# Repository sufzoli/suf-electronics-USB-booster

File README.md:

# suf-electronics-USB-booster
Boost power supply for inline conditioning of the 5V USB supply voltage

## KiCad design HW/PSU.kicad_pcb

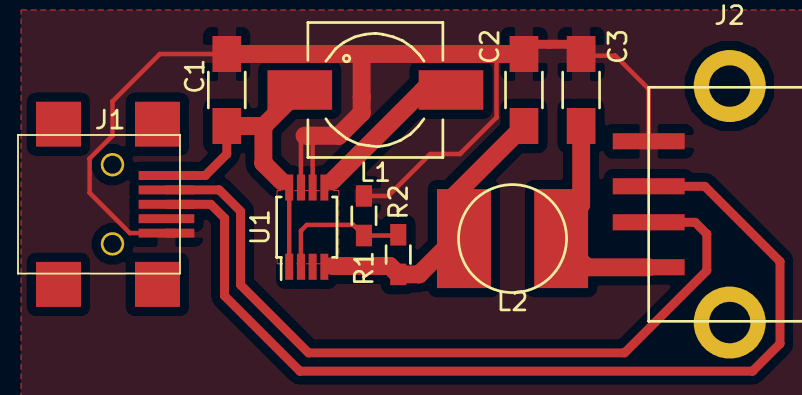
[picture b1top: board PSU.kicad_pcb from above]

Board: 2 copper layers, 10 parts (0 on the bottom side), 8 nets.

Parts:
C1, C2, C3: 22uF/10V; C_1206_HandSoldering
J1: USB-MINI; A-USBB-M5-SMD
J2: USB_2; USB-A_SMD
L1: 4,7uH; Choke_SMD_Wuerth-WE-PD-Typ-M-Typ-S_Handsoldering
L2: 1uH; PCD0504_Handsoldering
R1: 470K; R_0603_HandSoldering
R2: 1,5M; R_0603_HandSoldering
U1: MCP1642D-ADJ; MSOP-8_3x3mm_Pitch0.65mm

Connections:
GND: C1.2, C2.2, C3.2, J1.5, J2.4, R1.2, U1.6, U1.7
unnamed: C2.1, L2.1, R2.2, U1.4
unnamed: J1.2, J2.2
unnamed: J1.3, J2.3
unnamed: L1.2, U1.5
unnamed: R1.1, R2.1, U1.2
VCC: C3.1, J2.1, L2.2
VDD: C1.1, J1.1, L1.1, U1.1, U1.8

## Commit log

2015-05-20 First HW version based on MCP1642
2015-06-06 PCB Errors corrected, some component size tweak.
2015-06-30 Changed the polarity of the USB Connector
